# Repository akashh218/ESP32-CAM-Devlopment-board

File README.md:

# ESP32-S3 Camera Development Board

A custom **4-layer ESP32-S3 camera development board** designed in **KiCad**, with a focus on compact PCB layout, signal integrity, power integrity, grounding, and practical embedded hardware development.

## Overview

This project involves the complete design of a compact ESP32-S3-based development board, from schematic design and component selection through PCB placement, routing, and DRC verification.

The board is designed to provide camera capture, local data storage, USB connectivity, serial debugging, GPIO expansion, and camera flash control in a compact form factor.

## Key Features

* Camera interface for image capture
* microSD interface for local image and data storage
* USB-C connectivity for programming and native USB communication
* UART-based serial debugging
* Automatic BOOT and RESET control
* Software-controlled camera flash
* GPIO expansion for external peripherals
* 3.3 V regulated power supply
* Local power decoupling and filtering
* Dedicated ground plane
* Ground stitching vias
* RF-aware ESP32 antenna keep-out
* Compact 4-layer PCB architecture

## PCB Design Approach

The PCB was designed with particular attention to:

* Component placement and functional grouping
* Camera signal routing
* USB differential-pair routing
* microSD signal routing
* Power distribution
* Grounding and return-current paths
* Decoupling capacitor placement
* Antenna clearance
* Via placement and ground stitching
* Manufacturing clearances
* DRC verification

GPIO assignments were also planned to simplify routing and reduce unnecessary trace crossings.

## Layer Stack-up

| Layer                    | Purpose                                         |
| ------------------------ | ----------------------------------------------- |
| **L1 – Top**             | Components and critical signal routing          |
| **L2 – GND**             | Continuous ground plane                         |
| **L3 – Power / Signals** | Power distribution and secondary signal routing |
| **L4 – Bottom**          | General signal routing and passive components   |

The dedicated ground plane provides a continuous reference for signal return paths and helps improve power and signal integrity.

## Design Challenges

Some of the main challenges during development included:

* Routing multiple camera signals within a compact PCB area
* Maintaining clean USB differential-pair routing
* Optimizing GPIO assignments for easier routing
* Managing power and ground distribution
* Maintaining the ESP32 antenna keep-out region
* Resolving PCB design-rule and footprint issues
* Balancing component density with manufacturability

## Tools

* **KiCad** – Schematic capture and PCB design
* **KiCad DRC** – Design-rule verification

## Repository Contents

This repository contains the design files associated with the project, including:

* Schematic files
* PCB layout files
* Footprints and libraries used by the design
* Design documentation
* Manufacturing files, if included

## Project Status

**PCB Design Completed**

The next stage is hardware fabrication and board bring-up, followed by testing of the power system, USB/UART programming, camera interface, microSD storage, and other peripherals.

## Learning Outcomes

This project strengthened my practical understanding of:

* PCB layout and routing
* Embedded hardware design
* Signal integrity
* Power integrity
* Grounding and return paths
* USB/UART interfaces
* RF-aware PCB design
* Component and footprint selection
* DRC debugging
* PCB manufacturability

---

Designed in KiCad | ESP32-S3 | 4-Layer PCB

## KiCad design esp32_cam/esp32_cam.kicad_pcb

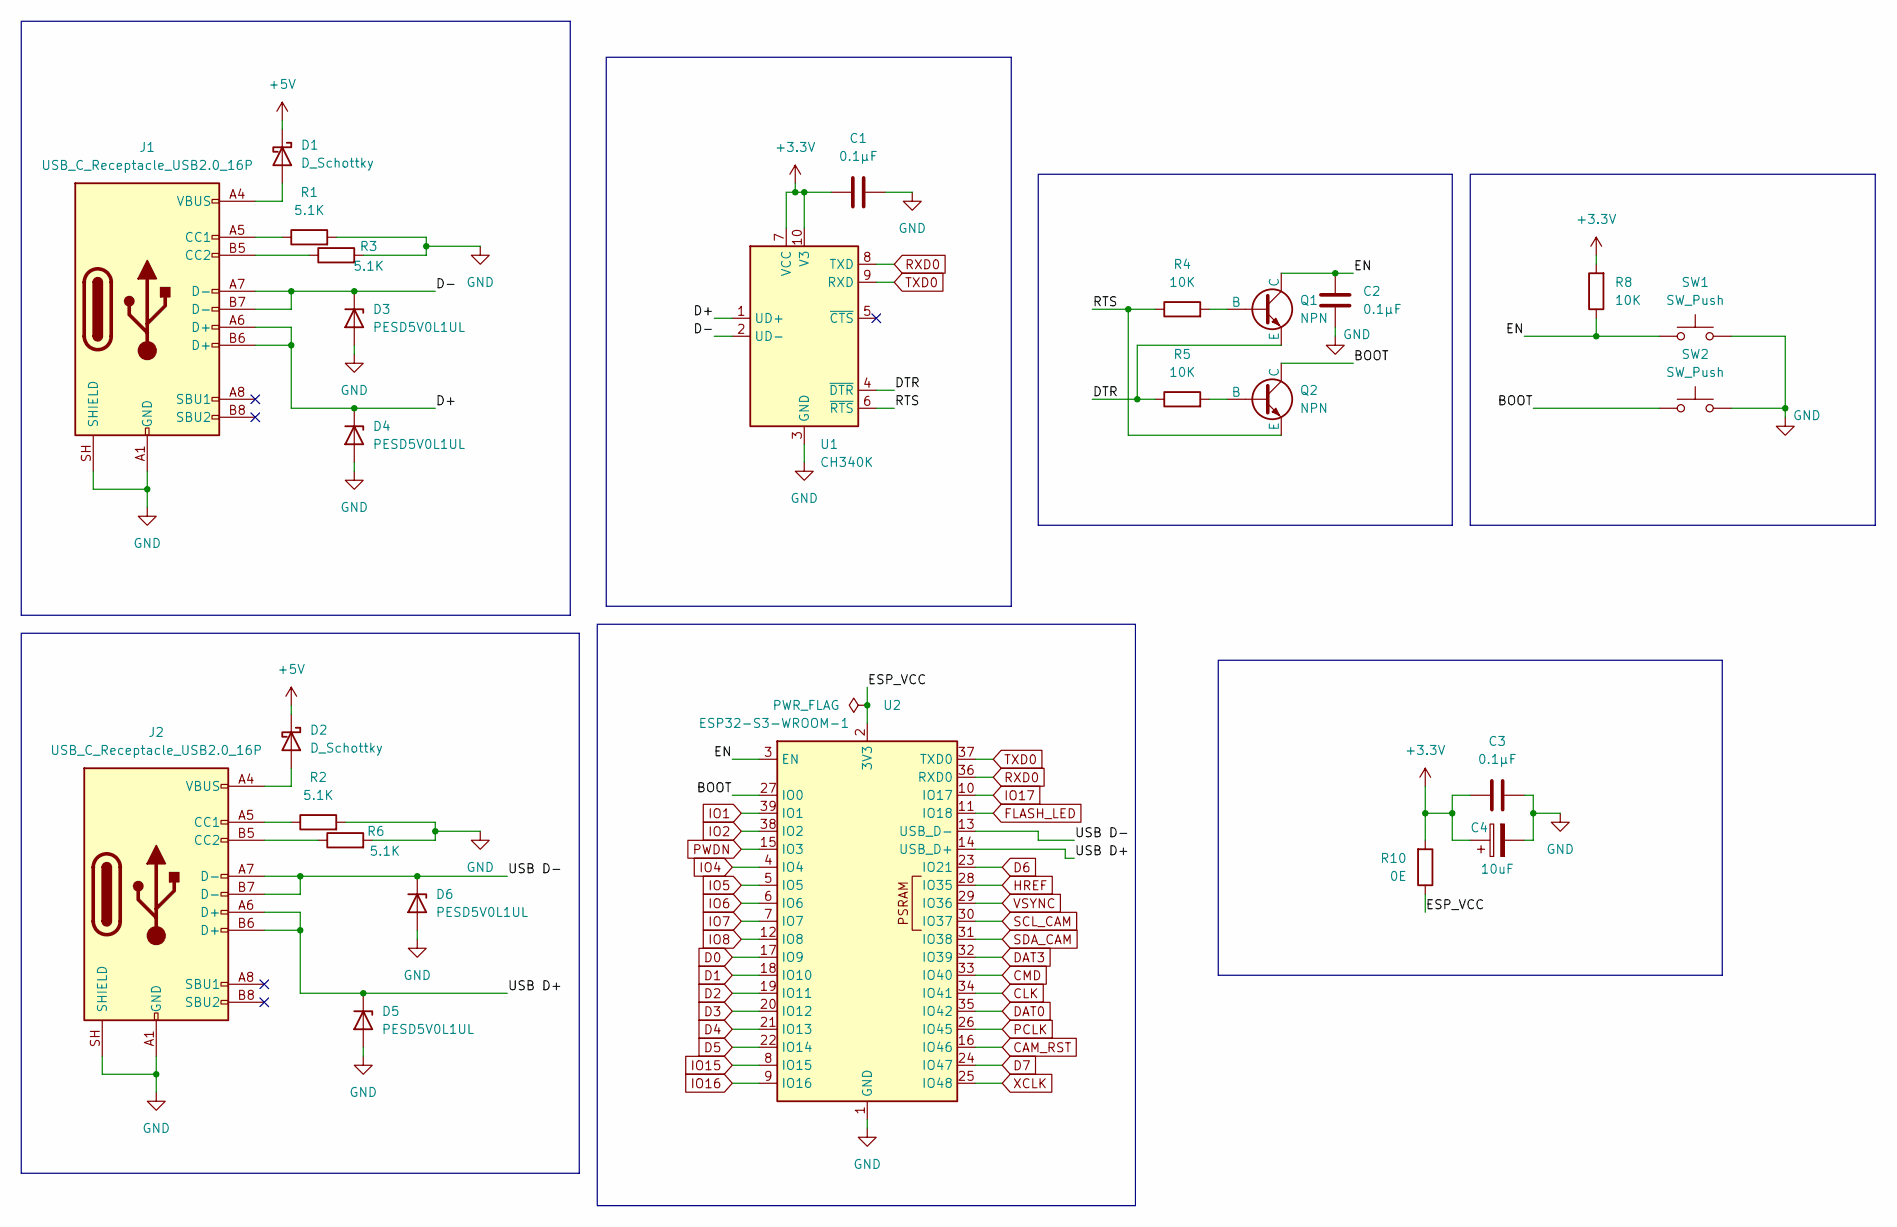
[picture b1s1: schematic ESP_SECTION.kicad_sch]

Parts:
C1, C2, C3: 0.1µF; C_0603_1608Metric
C4: 10uF; C_0603_1608Metric
D1, D2: D_Schottky; D_SOD-123
D3, D4, D5, D6: PESD5V0L1UL; D_SOD-882
J1, J2: USB_C_Receptacle_USB2.0_16P; USB_C_Receptacle_GCT_USB4105-xx-A_16P_TopMnt_Horizontal
Q1, Q2: NPN; SOT-23
R1, R2, R3, R6: 5.1K; R_0805_2012Metric
R4, R5, R8: 10K; R_0805_2012Metric
R10: 0E; R_0805_2012Metric
SW1, SW2: SW_Push; SW_Push_SPST_NO_Alps_SKRK
U1: CH340K; SSOP-10-1EP_3.9x4.9mm_P1mm_EP2.1x3.3mm
U2: ESP32-S3-WROOM-1

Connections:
+3.3V: C1.1, C3.1, C4.1, R8.2, R10.2, U1.7 (VCC), U1.10 (V3); also elsewhere on the board
+5V: D1.1 (K), D2.1 (K); also elsewhere on the board
/ESP_SECTION/BOOT: Q2.1 (C), SW2.1, U2.27 (IO0); also elsewhere on the board
/ESP_SECTION/D+: D4.1 (K), J1.A6 (D+), J1.B6 (D+), U1.1 (UD+)
/ESP_SECTION/D-: D3.1 (K), J1.A7 (D-), J1.B7 (D-), U1.2 (UD-)
/ESP_SECTION/DTR: Q1.3 (E), R5.1, U1.4 (~DTR)
/ESP_SECTION/EN: C2.1, Q1.1 (C), R8.1, SW1.1, U2.3 (EN)
/ESP_SECTION/ESP_VCC: R10.1, U2.2 (3V3)
/ESP_SECTION/RTS: Q2.3 (E), R4.1, U1.6 (~RTS)
/ESP_SECTION/USB D+: D5.1 (K), J2.A6 (D+), J2.B6 (D+), U2.14 (USB_D+)
/ESP_SECTION/USB D-: D6.1 (K), J2.A7 (D-), J2.B7 (D-), U2.13 (USB_D-)
CAM_RST: U2.16 (IO46); also elsewhere on the board
CLK: U2.34 (IO41); also elsewhere on the board
CMD: U2.33 (IO40); also elsewhere on the board
D0: U2.17 (IO9); also elsewhere on the board
D1: U2.18 (IO10); also elsewhere on the board
D2: U2.19 (IO11); also elsewhere on the board
D3: U2.20 (IO12); also elsewhere on the board
D4: U2.21 (IO13); also elsewhere on the board
D5: U2.22 (IO14); also elsewhere on the board
D6: U2.23 (IO21); also elsewhere on the board
D7: U2.24 (IO47); also elsewhere on the board
DAT0: U2.35 (IO42); also elsewhere on the board
DAT3: U2.32 (IO39); also elsewhere on the board
FLASH_LED: U2.11 (IO18); also elsewhere on the board
GND: C1.2, C2.2, C3.2, C4.2, D3.2 (A), D4.2 (A), D5.2 (A), D6.2 (A), J1.A1 (GND), J1.A12 (GND), J1.B1 (GND), J1.B12 (GND), J1.SH (SHIELD), J2.A1 (GND), J2.A12 (GND), J2.B1 (GND), J2.B12 (GND), J2.SH (SHIELD), R1.2, R2.2, R3.2, R6.2, SW1.2, SW2.2, U1.3 (GND), U1.11 (GND), U2.1 (GND), U2.40 (GND), U2.41 (GND); also elsewhere on the board
HREF: U2.28 (IO35); also elsewhere on the board
IO1: U2.39 (IO1); also elsewhere on the board
IO2: U2.38 (IO2); also elsewhere on the board
IO4: U2.4 (IO4); also elsewhere on the board
IO5: U2.5 (IO5); also elsewhere on the board
IO6: U2.6 (IO6); also elsewhere on the board
IO7: U2.7 (IO7); also elsewhere on the board
IO8: U2.12 (IO8); also elsewhere on the board
IO15: U2.8 (IO15); also elsewhere on the board
IO16: U2.9 (IO16); also elsewhere on the board
IO17: U2.10 (IO17); also elsewhere on the board
unnamed: D1.2 (A), J1.A4 (VBUS), J1.A9 (VBUS), J1.B4 (VBUS), J1.B9 (VBUS)
unnamed: D2.2 (A), J2.A4 (VBUS), J2.A9 (VBUS), J2.B4 (VBUS), J2.B9 (VBUS)
unnamed: J1.A5 (CC1), R1.1
unnamed: J1.B5 (CC2), R3.1
unnamed: J2.A5 (CC1), R2.1
unnamed: J2.B5 (CC2), R6.1
unnamed: Q1.2 (B), R4.2
unnamed: Q2.2 (B), R5.2
PCLK: U2.26 (IO45); also elsewhere on the board
PWDN: U2.15 (IO3); also elsewhere on the board
RXD0: U1.8 (TXD), U2.36 (RXD0); also elsewhere on the board
SCL_CAM: U2.30 (IO37); also elsewhere on the board
SDA_CAM: U2.31 (IO38); also elsewhere on the board
TXD0: U1.9 (RXD), U2.37 (TXD0); also elsewhere on the board
VSYNC: U2.29 (IO36); also elsewhere on the board
XCLK: U2.25 (IO48); also elsewhere on the board

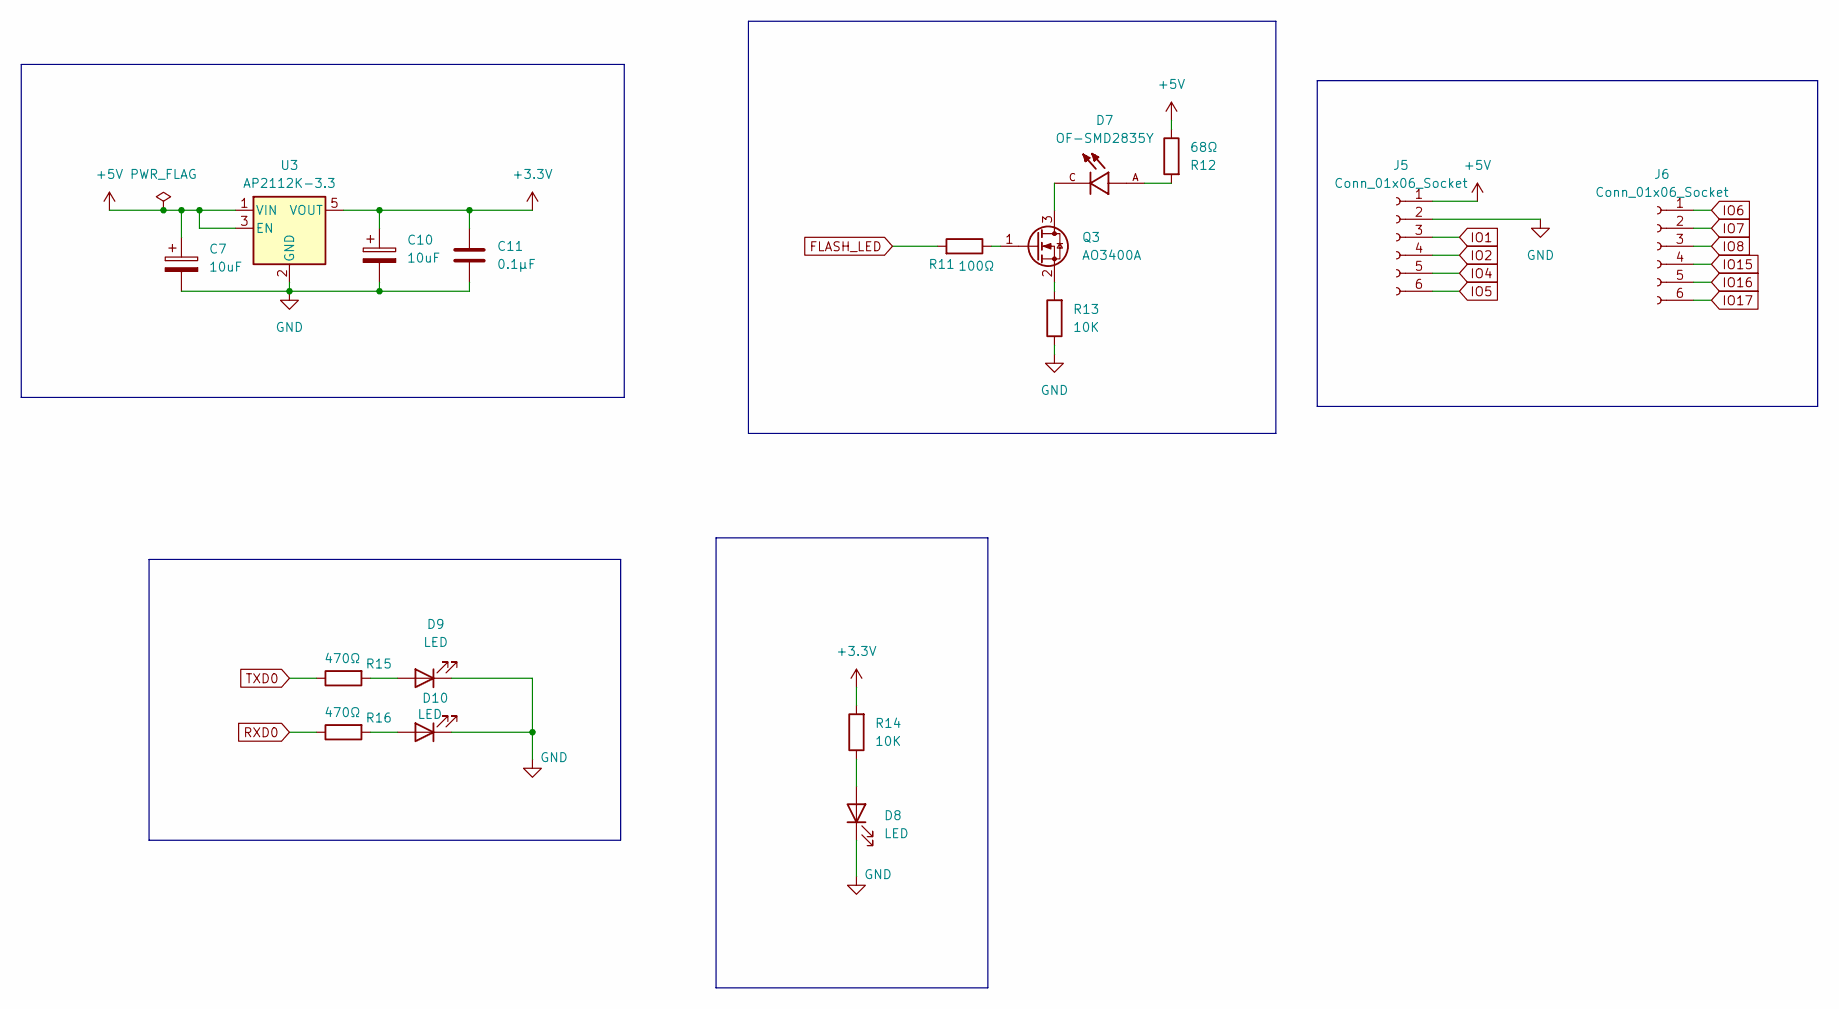
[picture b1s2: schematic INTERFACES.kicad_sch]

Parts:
C7, C10: 10uF; C_0805_2012Metric
C11: 0.1µF; C_0603_1608Metric
D7: OF-SMD2835Y; LED_OF-SMD2835Y; PARTREV N/A
D8, D9, D10: LED; D_0805_2012Metric
J5, J6: Conn_01x06_Socket; PinHeader_1x06_P2.54mm_Vertical
Q3: AO3400A; SOT-23
R11: 100Ω; R_0805_2012Metric
R12: 68Ω; R_0805_2012Metric
R13, R14: 10K; R_0805_2012Metric
R15, R16: 470Ω; R_0805_2012Metric
U3: AP2112K-3.3; SOT-23-5

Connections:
+3.3V: C10.1, C11.1, R14.2, U3.5 (VOUT); also elsewhere on the board
+5V: C7.1, J5.1, R12.1, U3.1 (VIN), U3.3 (EN); also elsewhere on the board
FLASH_LED: R11.2; also elsewhere on the board
GND: C7.2, C10.2, C11.2, D8.1 (K), D9.1 (K), D10.1 (K), J5.2, R13.1, U3.2 (GND); also elsewhere on the board
IO1: J5.3; also elsewhere on the board
IO2: J5.4; also elsewhere on the board
IO4: J5.5; also elsewhere on the board
IO5: J5.6; also elsewhere on the board
IO6: J6.1; also elsewhere on the board
IO7: J6.2; also elsewhere on the board
IO8: J6.3; also elsewhere on the board
IO15: J6.4; also elsewhere on the board
IO16: J6.5; also elsewhere on the board
IO17: J6.6; also elsewhere on the board
unnamed: D7.A, R12.2
unnamed: D8.2 (A), R14.1
unnamed: D9.2 (A), R15.2
unnamed: D10.2 (A), R16.2
unnamed: D7.C, Q3.3 (D)
unnamed: Q3.1 (G), R11.1
unnamed: Q3.2 (S), R13.2
RXD0: R16.1; also elsewhere on the board
TXD0: R15.1; also elsewhere on the board

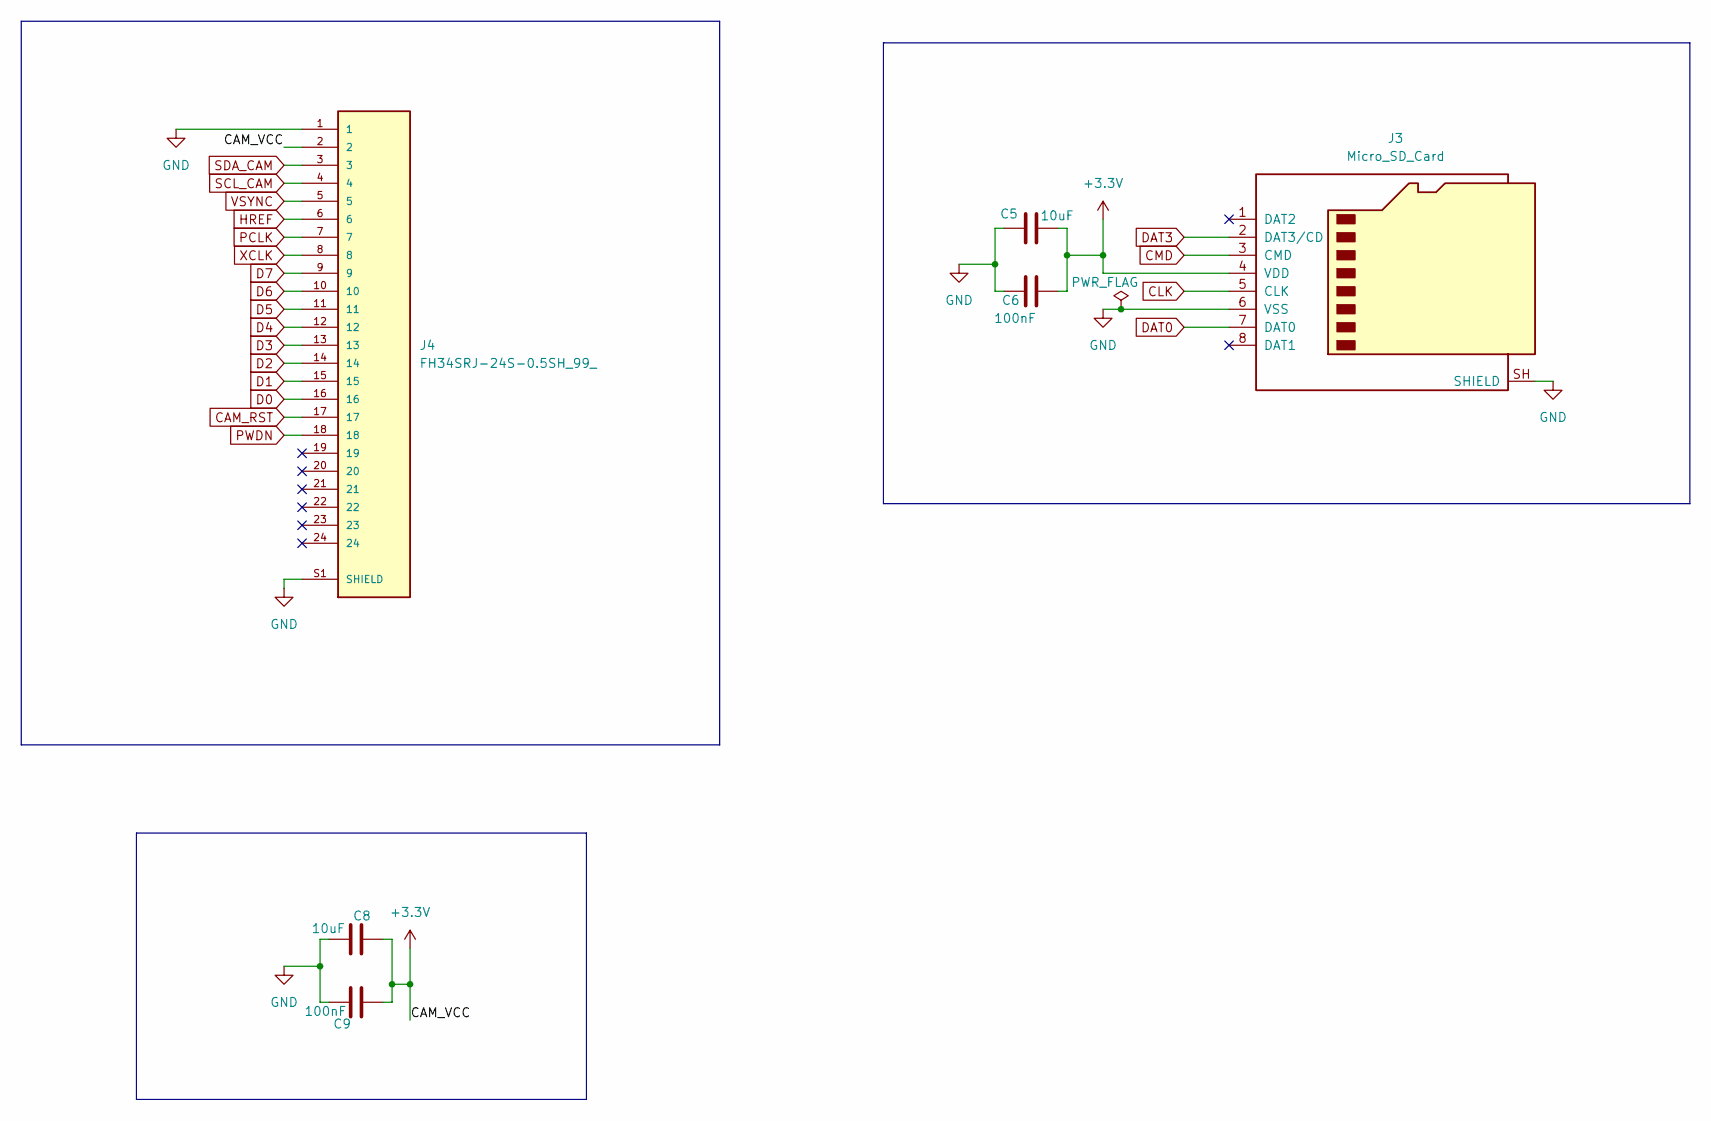
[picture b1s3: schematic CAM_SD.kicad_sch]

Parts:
C5: 10uF; C_0603_1608Metric
C6, C9: 100nF; C_0603_1608Metric
C8: 10uF; C_0805_2012Metric
J3: Micro_SD_Card; microSD_HC_Hirose_DM3BT-DSF-PEJS
J4: FH34SRJ-24S-0.5SH_99_; HRS_FH34SRJ-24S-0.5SH_99_; PARTREV NA

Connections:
+3.3V: C5.1, C6.1, C8.2, C9.2, J3.4 (VDD), J4.2; also elsewhere on the board
CAM_RST: J4.17; also elsewhere on the board
CLK: J3.5 (CLK); also elsewhere on the board
CMD: J3.3 (CMD); also elsewhere on the board
D0: J4.16; also elsewhere on the board
D1: J4.15; also elsewhere on the board
D2: J4.14; also elsewhere on the board
D3: J4.13; also elsewhere on the board
D4: J4.12; also elsewhere on the board
D5: J4.11; also elsewhere on the board
D6: J4.10; also elsewhere on the board
D7: J4.9; also elsewhere on the board
DAT0: J3.7 (DAT0); also elsewhere on the board
DAT3: J3.2 (DAT3/CD); also elsewhere on the board
GND: C5.2, C6.2, C8.1, C9.1, J3.6 (VSS), J3.SH (SHIELD), J4.1, J4.S1 (SHIELD), J4.S2 (SHIELD); also elsewhere on the board
HREF: J4.6; also elsewhere on the board
PCLK: J4.7; also elsewhere on the board
PWDN: J4.18; also elsewhere on the board
SCL_CAM: J4.4; also elsewhere on the board
SDA_CAM: J4.3; also elsewhere on the board
VSYNC: J4.5; also elsewhere on the board
XCLK: J4.8; also elsewhere on the board

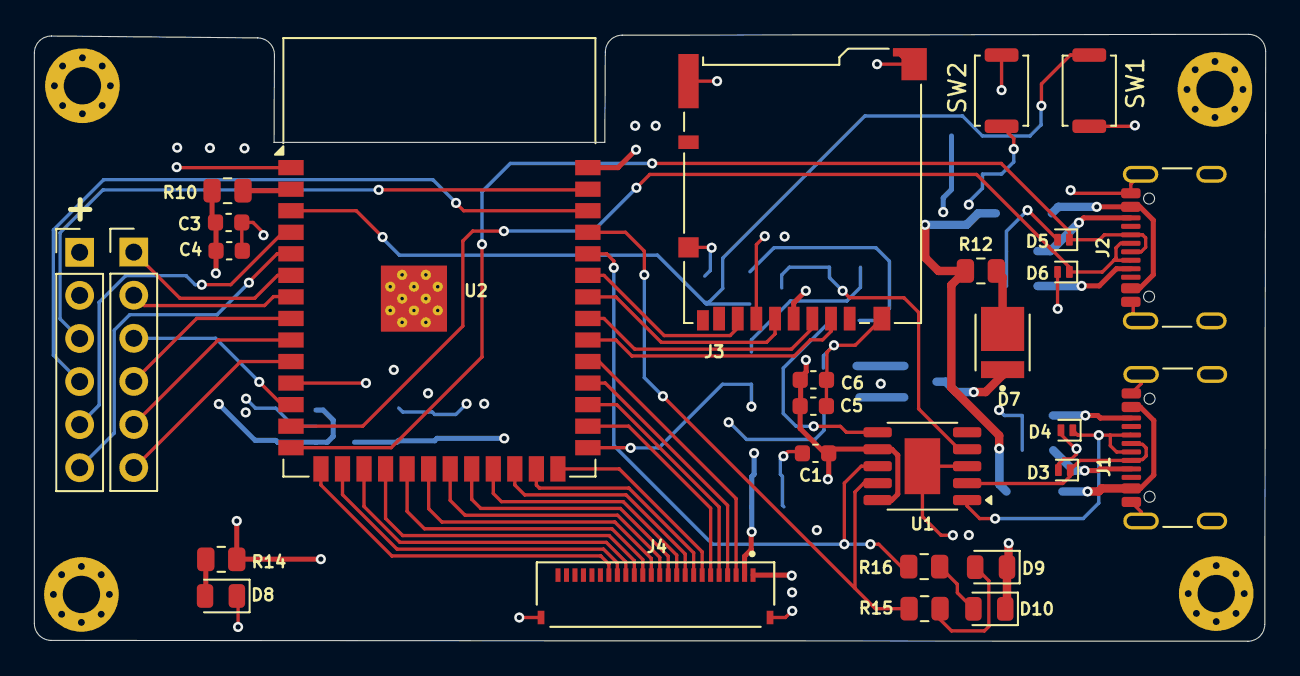
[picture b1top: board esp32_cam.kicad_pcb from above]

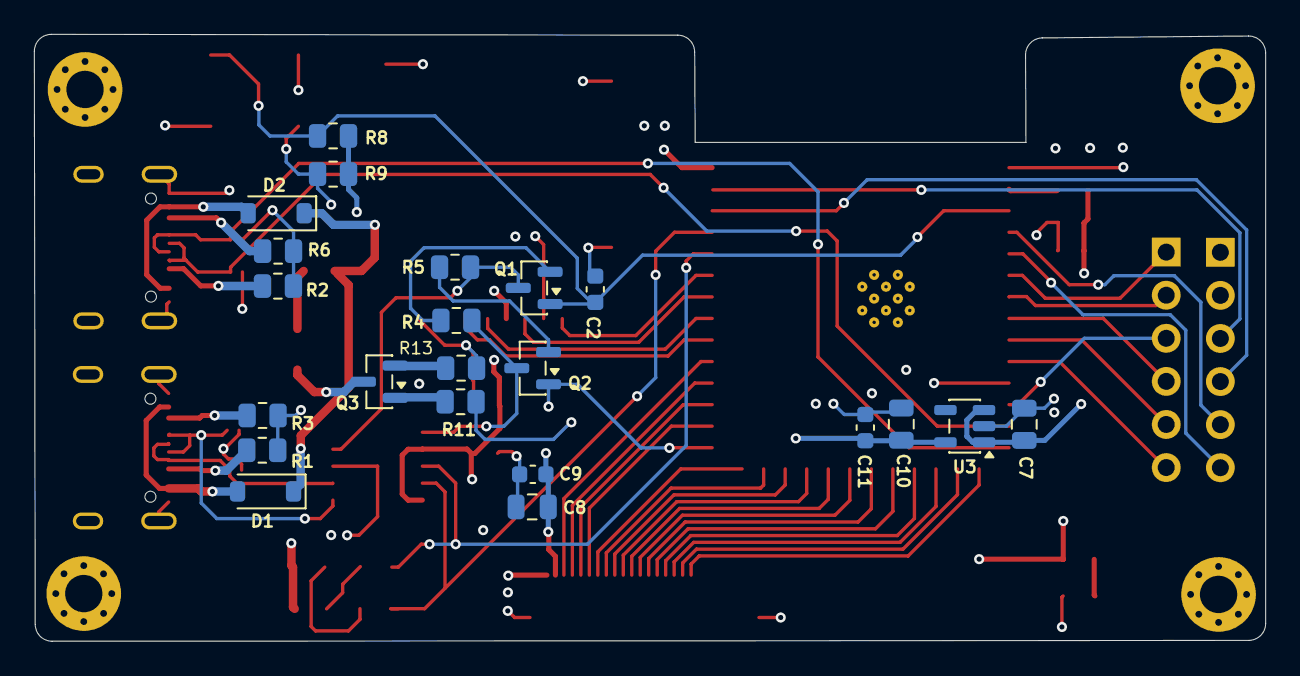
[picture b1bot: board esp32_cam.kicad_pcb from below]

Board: 4 copper layers, 72.6 x 35.8 mm, 50 parts (22 on the bottom side), 60 nets.

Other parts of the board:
R9: 10K; R_0805_2012Metric

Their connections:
+3.3V: R9.1; also elsewhere on the board
/ESP_SECTION/BOOT: R9.2; also elsewhere on the board
